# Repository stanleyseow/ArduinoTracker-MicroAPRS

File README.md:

Arduino APRS SVTrackR
=====================

 - Written by Stanley Seow ( 9W2SVT / N5SVT )
 - e-mail : stanleyseow@gmail.com
 
 *** Pls refer to the top of the source code for version history and updated instructions.

 This sketch configure the MicroAPRS (the modem) for the proper callsign and ssid and read/write data coming in from the MicroAPRS (another Arduino/atmega328P with bootloader) via Serial port

 Library needed :-
 
 * AltSoftSerial ( https://www.pjrc.com/teensy/td_libs_AltSoftSerial.html )
 * tinyGPS++ ( http://arduiniana.org/libraries/tinygpsplus/ )
 * SSD1306 OLED Text only ( https://github.com/stanleyseow/ArduinoTracker-MicroAPRS/tree/master/libraries/SSD1306_text )
 * MicroAPRS libs 
 
 Instructions :-
 
 Download the MicroAPRS compiled Modem.hex from https://github.com/markqvist/MicroAPRS/
 
 As this hex is not compiled from the Arduino IDE, you need to manually upload this hex to the Arduino with a bootloader using avrdude or Xloader.
 
Xloader to load this hex image to the Arduino / Mini Pro :-
 
    1. Download the Xloader : http://russemotto.com/xloader/
    2. Copy modem.hex into Xloader folder
    3. Select the modem hex file 
    4. Select UNO for UNO or Duemilanove/328 for Mini Pro
    5. Select the COM port and press Upload

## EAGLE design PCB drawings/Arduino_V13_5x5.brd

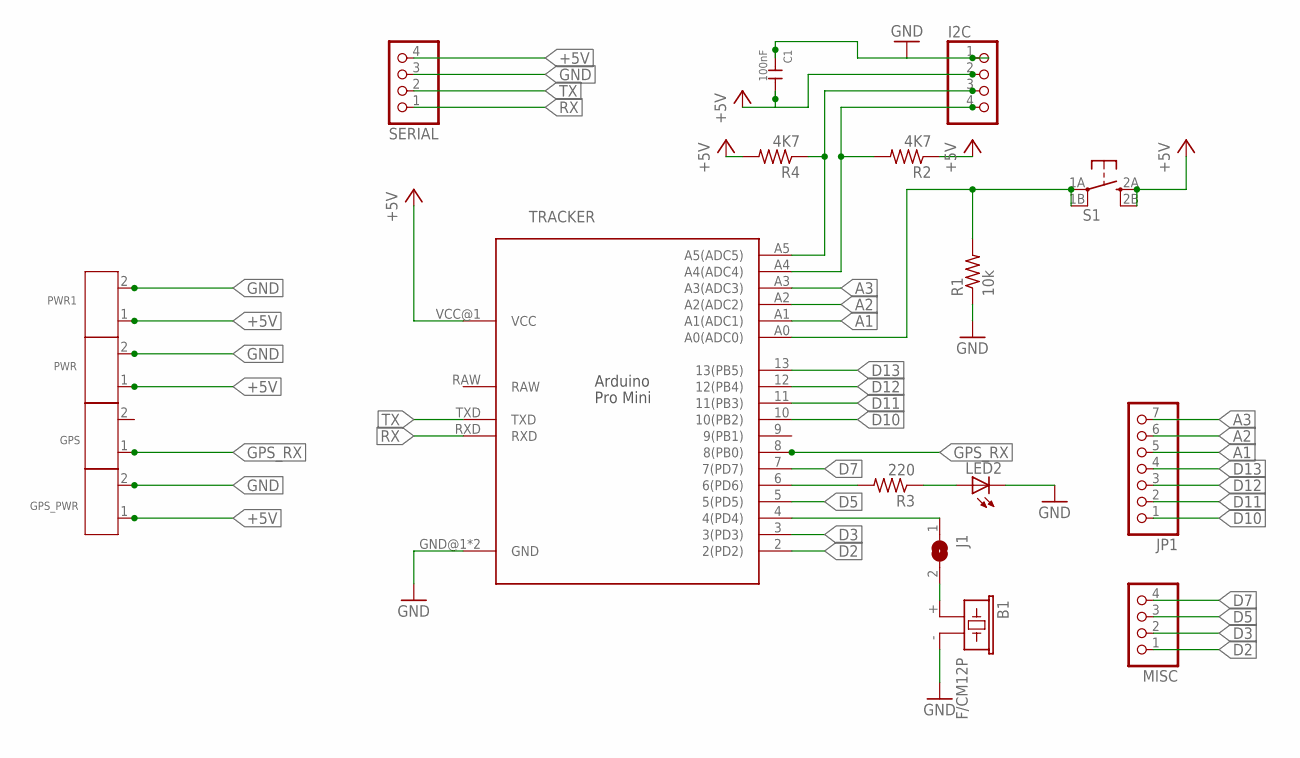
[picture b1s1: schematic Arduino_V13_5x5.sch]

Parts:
B1: F/CM12P
C1: 100nF; C1206
GPS: SCREW-TERMINAL-GREEN(2P-3.5); H2-3.5-7.0X7.0MM
GPS_PWR: SCREW-TERMINAL-GREEN(2P-3.5); H2-3.5-7.0X7.0MM
I2C: PINHD-1X4; 1X04
J1: SJ
JP1: PINHD-1X7; 1X07
LED2: LED5MM
MISC: PINHD-1X4; 1X04
PWR, PWR1: SCREW-TERMINAL-GREEN(2P-3.5); H2-3.5-7.0X7.0MM
R1: 10k; M1206
R2, R4: 4K7; M1206
R3: 220; M1206
S1: TACTILETACT-6X6-PTH; TACTILE-PTH
SERIAL: PINHD-1X4; 1X04
TRACKER: PRO-MINI

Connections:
+5V: C1.2, GPS_PWR.1, I2C.2, PWR.1, PWR1.1, R2.1, R4.2, S1.2A, S1.2B, SERIAL.4, TRACKER.VCC@1 (VCC)
A1: JP1.5, TRACKER.A1 (A1(ADC1))
A2: JP1.6, TRACKER.A2 (A2(ADC2))
A3: JP1.7, TRACKER.A3 (A3(ADC3))
A4: I2C.4, R2.2, TRACKER.A4 (A4(ADC4))
BUTTON: R1.2, S1.1A, S1.1B, TRACKER.A0 (A0(ADC0))
BUZZER: J1.1, TRACKER.4 (4(PD4))
D2: MISC.1, TRACKER.2 (2(PD2))
D3: MISC.2, TRACKER.3 (3(PD3))
D5: MISC.3, TRACKER.5 (5(PD5))
D7: MISC.4, TRACKER.7 (7(PD7))
D10: JP1.1, TRACKER.10 (10(PB2))
D11: JP1.2, TRACKER.11 (11(PB3))
D12: JP1.3, TRACKER.12 (12(PB4))
D13: JP1.4, TRACKER.13 (13(PB5))
GND: B1.- (2), C1.1, GPS_PWR.2, I2C.1, LED2.K (C), PWR.2, PWR1.2, R1.1, SERIAL.3, TRACKER.GND@1 (GND), TRACKER.GND@2 (GND)
GPS_RX: GPS.1, TRACKER.8 (8(PB0))
unnamed: I2C.3, R4.1, TRACKER.A5 (A5(ADC5))
unnamed: LED2.A, R3.1
unnamed: R3.2, TRACKER.6 (6(PD6))
unnamed: B1.+ (1), J1.2
RX: SERIAL.1, TRACKER.RXD
TX: SERIAL.2, TRACKER.TXD

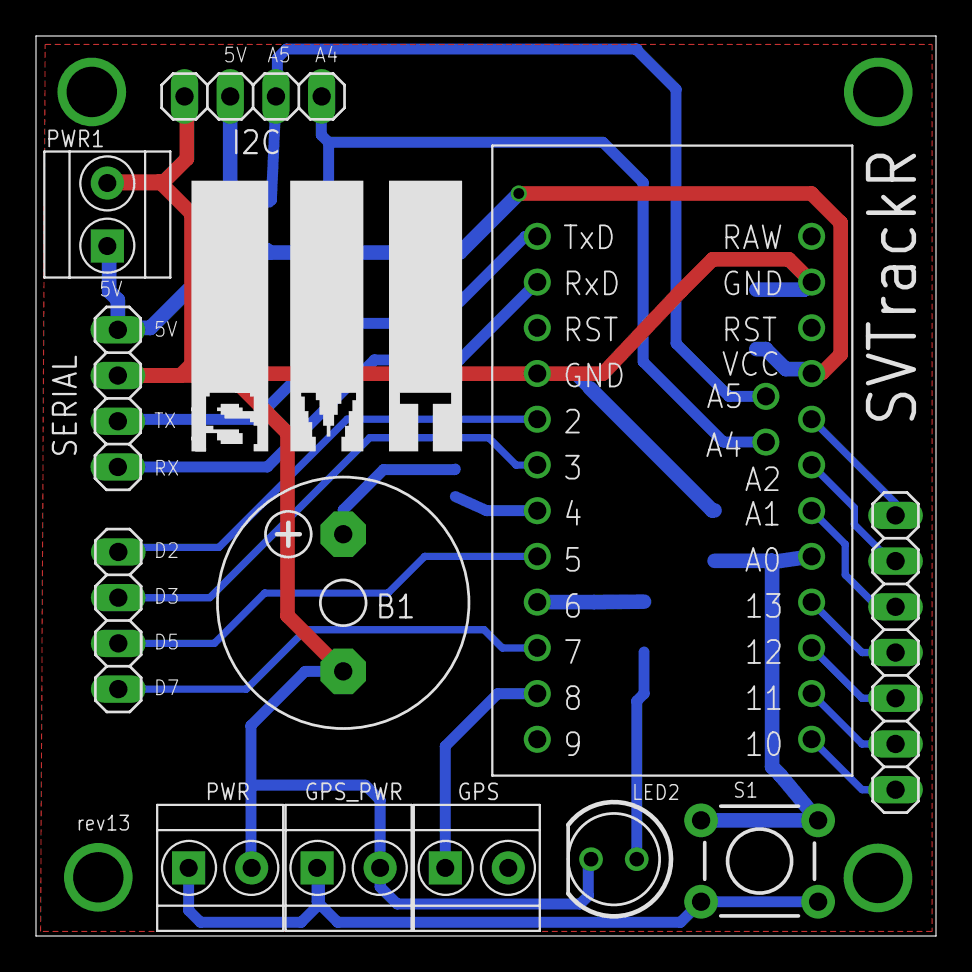
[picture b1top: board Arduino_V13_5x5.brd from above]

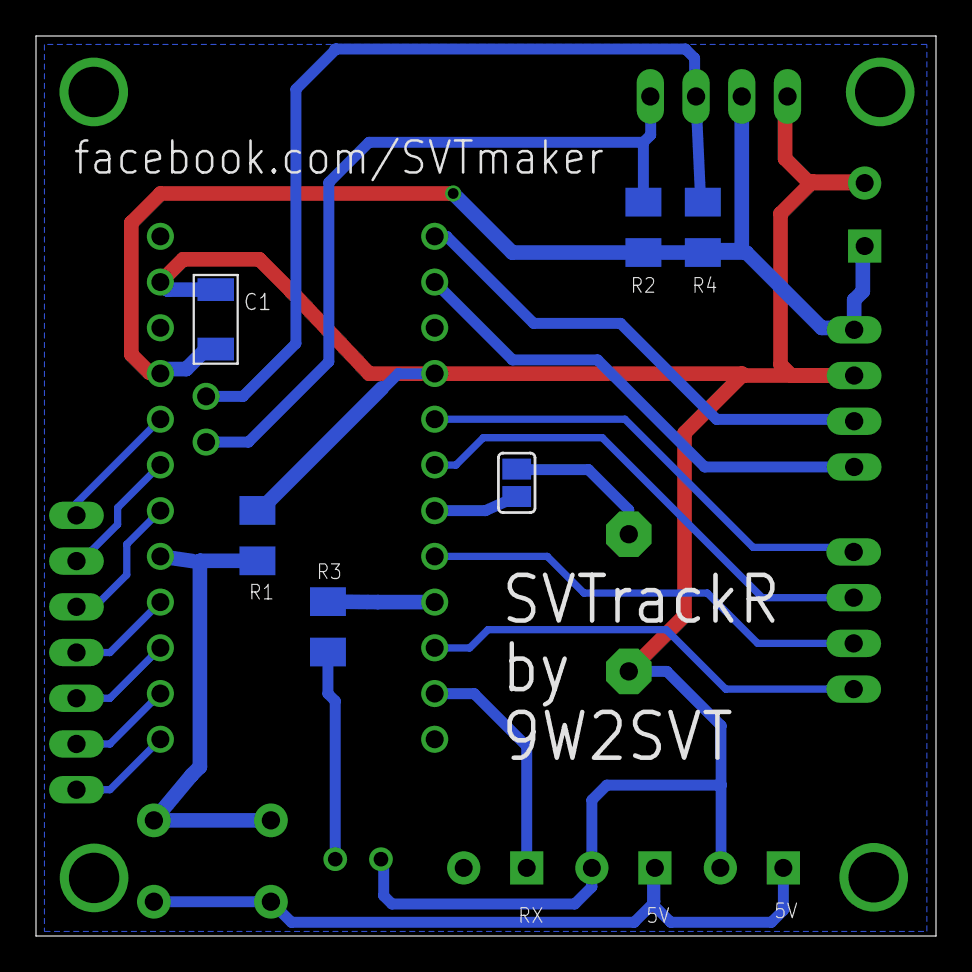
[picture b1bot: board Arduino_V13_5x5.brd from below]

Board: 2 copper layers, 50.0 x 50.0 mm, 18 parts (6 on the bottom side), 23 nets.

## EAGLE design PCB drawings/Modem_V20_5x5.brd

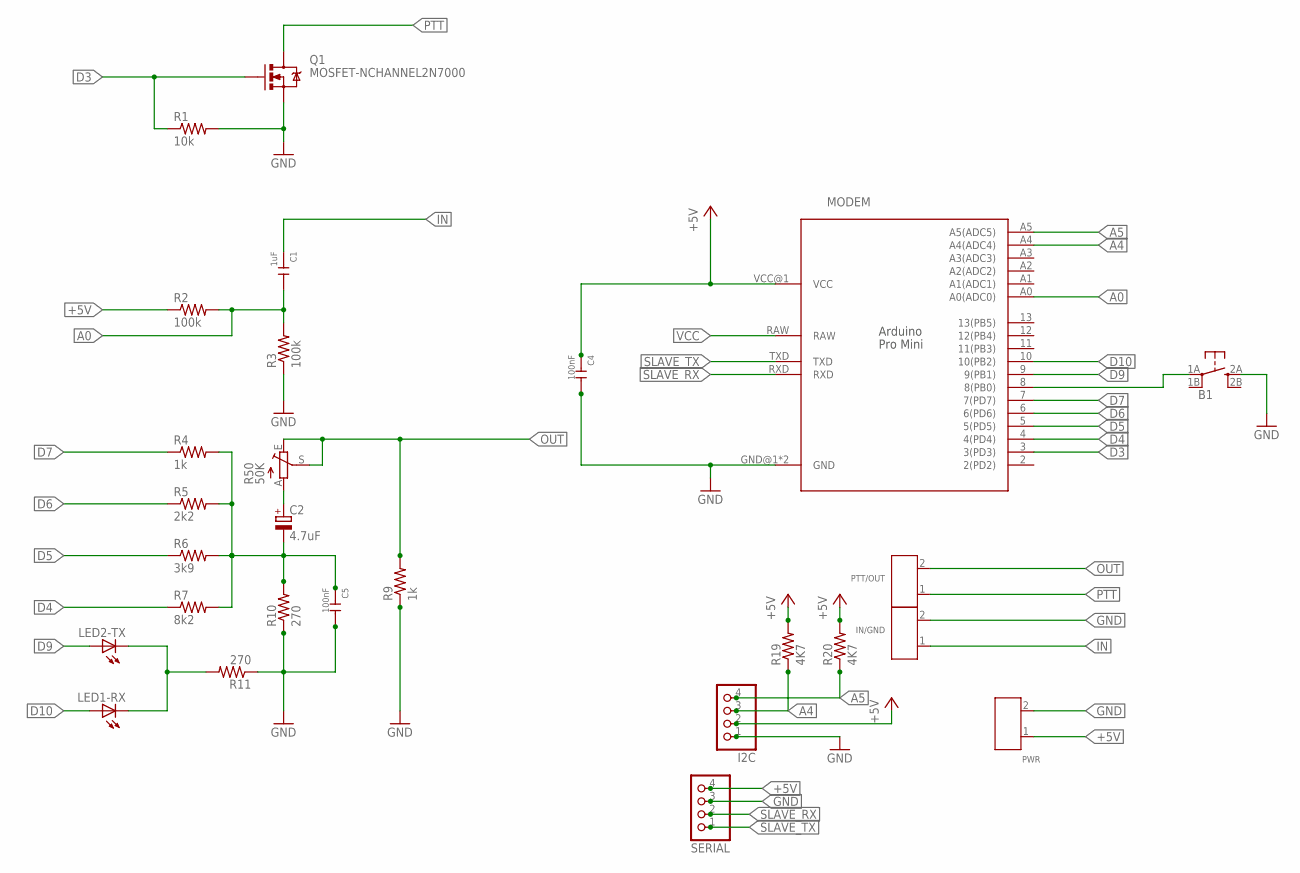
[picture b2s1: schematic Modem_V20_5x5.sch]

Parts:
B1: TACTILETACT-6X6-PTH; TACTILE-PTH
C1: 1uF; C1206
C2: 4.7uF; E2,5-6
C4, C5: 100nF; C1206
I2C: PINHD-1X4; 1X04
IN/GND: SCREW-TERMINAL-GREEN(2P-3.5); H2-3.5-7.0X7.0MM
LED1-RX, LED2-TX: LED1206; LED-1206
MODEM: PRO-MINI
PTT/OUT: SCREW-TERMINAL-GREEN(2P-3.5); H2-3.5-7.0X7.0MM
PWR: SCREW-TERMINAL-GREEN(2P-3.5); H2-3.5-7.0X7.0MM
Q1: MOSFET-NCHANNEL2N7000; TO-92
R1: 10k; R1206
R2, R3: 100k; R1206
R4, R9: 1k; R1206
R5: 2k2; R1206
R6: 3k9; R1206
R7: 8k2; R1206
R10, R11: 270; R1206
R19, R20: 4K7; R1206
R50: 50K; CA6V
SERIAL: PINHD-1X4; 1X04

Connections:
+5V: C4.1, I2C.2, MODEM.VCC@1 (VCC), PWR.1, R2.1, R19.2, R20.2, SERIAL.4
A0: C1.2, MODEM.A0 (A0(ADC0)), R2.2, R3.2
A4: I2C.3, MODEM.A4 (A4(ADC4)), R19.1
A5: I2C.4, MODEM.A5 (A5(ADC5)), R20.1
D3: MODEM.3 (3(PD3)), Q1.2 (G), R1.1
D4: MODEM.4 (4(PD4)), R7.1
D5: MODEM.5 (5(PD5)), R6.1
D6: MODEM.6 (6(PD6)), R5.1
D7: MODEM.7 (7(PD7)), R4.1
D8: B1.1A, MODEM.8 (8(PB0))
D9: LED2-TX.A, MODEM.9 (9(PB1))
D10: LED1-RX.A, MODEM.10 (10(PB2))
GND: B1.2A, C4.2, C5.2, I2C.1, IN/GND.2, MODEM.GND@1 (GND), MODEM.GND@2 (GND), PWR.2, Q1.1 (S), R1.2, R3.1, R9.1, R10.1, R11.1, SERIAL.3
IN: C1.1, IN/GND.1
unnamed: C2.+, R50.A
unnamed: LED1-RX.C, LED2-TX.C, R11.2
unnamed: C2.-, C5.1, R4.2, R5.2, R6.2, R7.2, R10.2
OUT: PTT/OUT.2, R9.2, R50.E, R50.S
PTT: PTT/OUT.1, Q1.3 (D)
SLAVE_RX: MODEM.RXD, SERIAL.2
SLAVE_TX: MODEM.TXD, SERIAL.1
VCC: MODEM.RAW

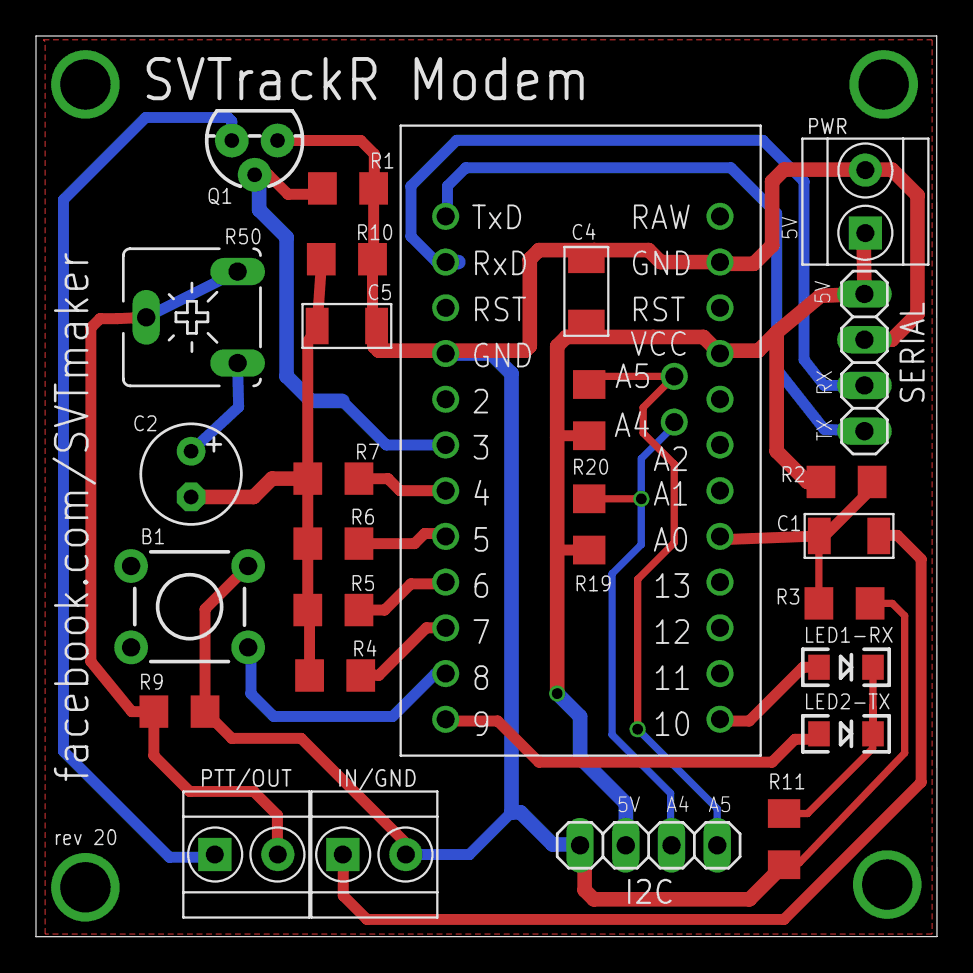
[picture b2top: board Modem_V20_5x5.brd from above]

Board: 2 copper layers, 50.1 x 50.0 mm, 27 parts (0 on the bottom side), 21 nets.

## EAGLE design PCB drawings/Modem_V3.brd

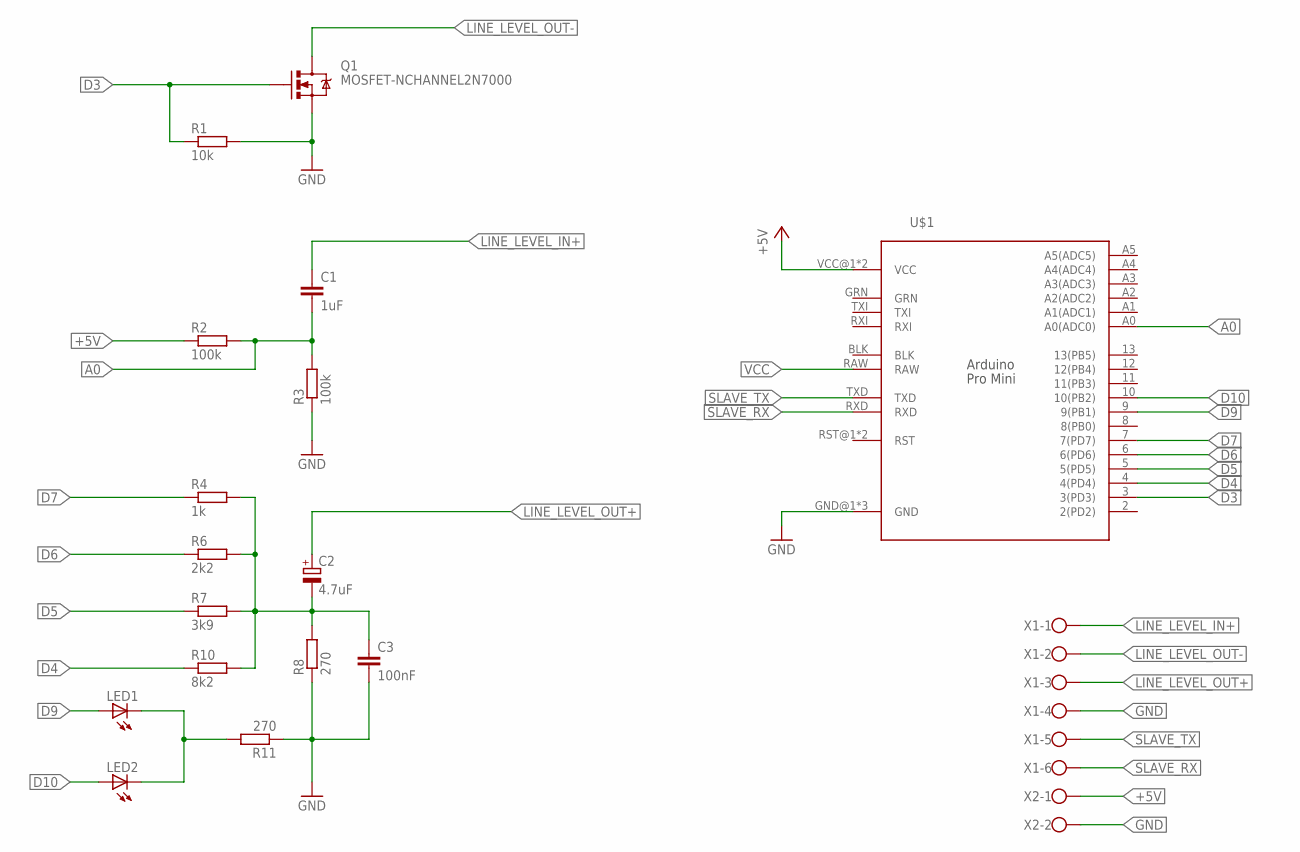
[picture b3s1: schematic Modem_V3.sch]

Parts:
C1: 1uF; C025-030X050
C2: 4.7uF; E2,5-6
C3: 100nF; C025-030X050
LED1, LED2: LED5MM
Q1: MOSFET-NCHANNEL2N7000; TO-92
R1: 10k; 0207/2V
R2, R3: 100k; 0207/2V
R4: 1k; 0207/2V
R6: 2k2; 0207/2V
R7: 3k9; 0207/2V
R8, R11: 270; 0207/2V
R10: 8k2; 0207/2V
U$1: PRO-MINI
X1: W237-6
X2: W237-102

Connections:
+5V: R2.1, U$1.VCC@1 (VCC), U$1.VCC@2 (VCC), X2.1
A0: C1.2, R2.2, R3.2, U$1.A0 (A0(ADC0))
D3: Q1.2 (G), R1.1, U$1.3 (3(PD3))
D4: R10.1, U$1.4 (4(PD4))
D5: R7.1, U$1.5 (5(PD5))
D6: R6.1, U$1.6 (6(PD6))
D7: R4.1, U$1.7 (7(PD7))
D9: LED1.A, U$1.9 (9(PB1))
D10: LED2.A, U$1.10 (10(PB2))
GND: C3.2, Q1.1 (S), R1.2, R3.1, R8.1, R11.1, U$1.GND@1 (GND), U$1.GND@2 (GND), U$1.GND@3 (GND), X1.4, X2.2
LINE_LEVEL_IN+: C1.1, X1.1
LINE_LEVEL_OUT+: C2.+, X1.3
LINE_LEVEL_OUT-: Q1.3 (D), X1.2
unnamed: LED1.K (C), LED2.K (C), R11.2
unnamed: C2.-, C3.1, R4.2, R6.2, R7.2, R8.2, R10.2
SLAVE_RX: U$1.RXD, X1.6
SLAVE_TX: U$1.TXD, X1.5
VCC: U$1.RAW

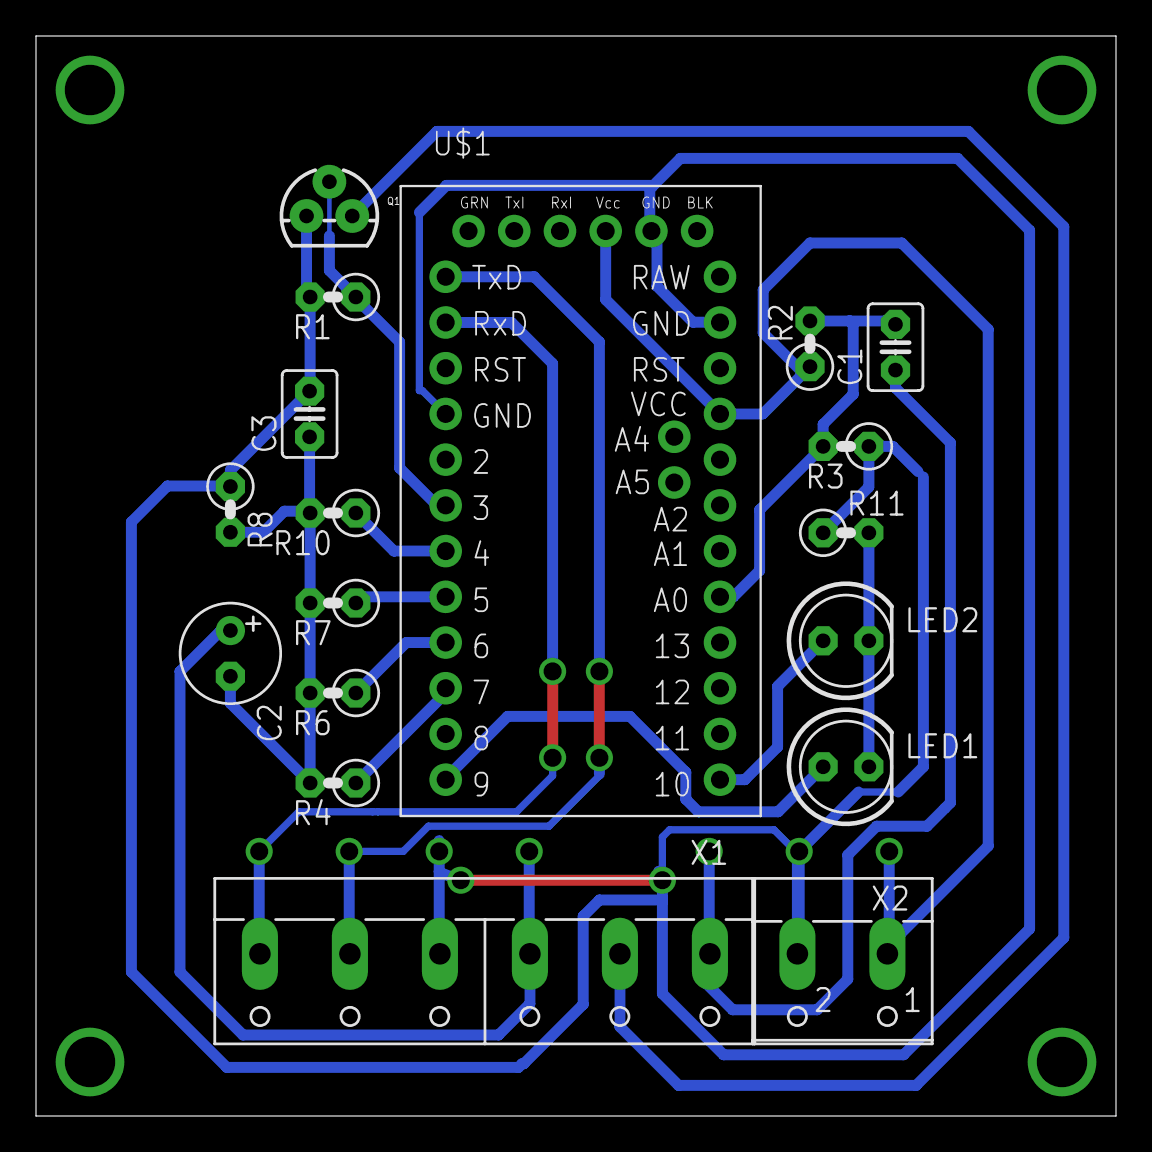
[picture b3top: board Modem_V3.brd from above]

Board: 2 copper layers, 60.0 x 60.0 mm, 18 parts (0 on the bottom side), 17 nets.

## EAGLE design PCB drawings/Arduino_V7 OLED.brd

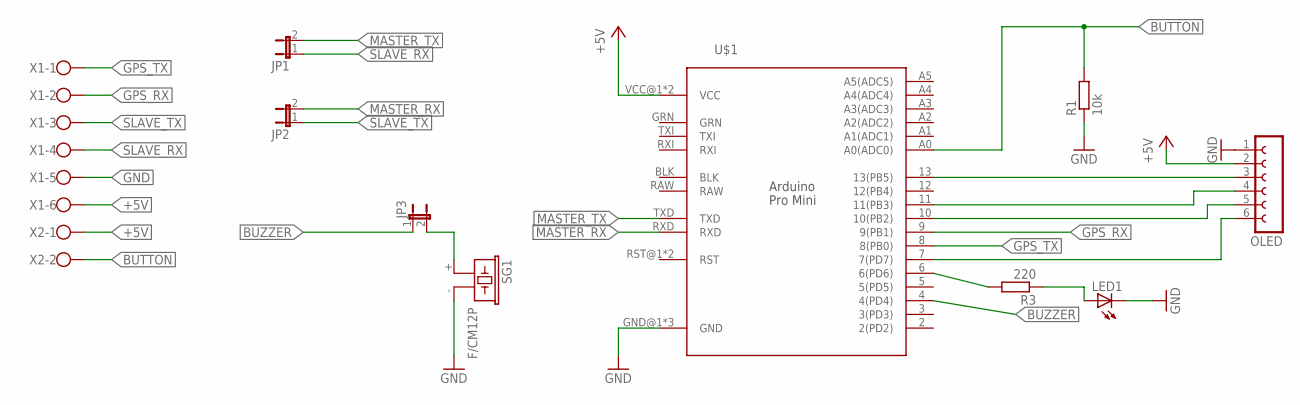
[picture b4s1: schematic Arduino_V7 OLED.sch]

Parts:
JP1, JP2, JP3: JP1E; JP1
LED1: LED5MM
OLED: FE06-1; FE06
R1: 10k; 0207/10
R3: 220; 0207/10
SG1: F/CM12P
U$1: PRO-MINI
X1: W237-6
X2: W237-102

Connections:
+5V: OLED.2, U$1.VCC@1 (VCC), U$1.VCC@2 (VCC), X1.6, X2.1
BUTTON: R1.2, U$1.A0 (A0(ADC0)), X2.2
BUZZER: JP3.1, U$1.4 (4(PD4))
CS: OLED.6, U$1.7 (7(PD7))
DI: OLED.4, U$1.11 (11(PB3))
GND: LED1.K (C), OLED.1, R1.1, SG1.- (2), U$1.GND@1 (GND), U$1.GND@2 (GND), U$1.GND@3 (GND), X1.5
GPS_RX: U$1.9 (9(PB1)), X1.2
GPS_TX: U$1.8 (8(PB0)), X1.1
MASTER_RX: JP2.2, U$1.RXD
MASTER_TX: JP1.2, U$1.TXD
unnamed: OLED.3, U$1.13 (13(PB5))
unnamed: LED1.A, R3.1
unnamed: R3.2, U$1.6 (6(PD6))
unnamed: JP3.2, SG1.+ (1)
RST: OLED.5, U$1.10 (10(PB2))
SLAVE_RX: JP1.1, X1.4
SLAVE_TX: JP2.1, X1.3

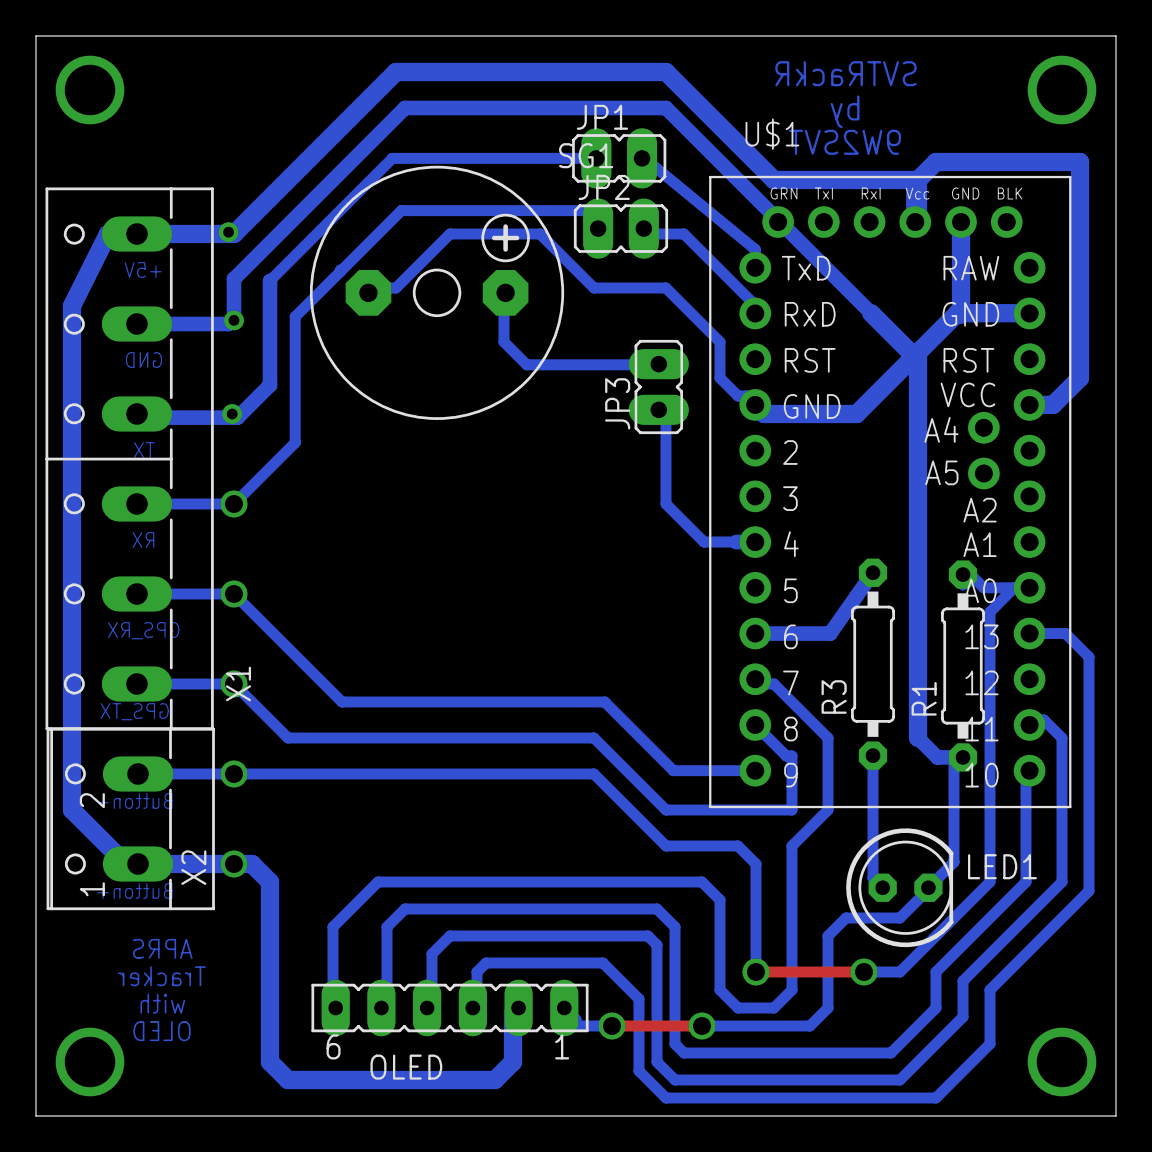
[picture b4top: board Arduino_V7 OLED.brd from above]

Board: 2 copper layers, 60.0 x 60.0 mm, 11 parts (0 on the bottom side), 17 nets.

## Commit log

2014-07-04 Initial commit
    This is the initial commit …
2014-07-04 Updated documentation...
2014-07-07 Updates and bug fixes
    Added check for gps lock, current speed and tx interval
2014-07-14 Updated to initial V0.3
    Added detection for headings and speed
2014-07-15 Updates and bug fixes 0.3a
    Fixes to course change formula
    Fixes to speed detection / Tx interval formula
    Added timestamp to debugging messages
2014-07-15 README updated
2014-07-17 Updates and bug fixes to txInternal timeout
2014-07-19 Updates to decodeAPRS() and LCD display
2014-07-22 Uploaded README
2014-08-03 Added #ifdef for LCD20x4, DEBUG and TFT22
    Added #defines, ported to Arduino Mini Pro 3.3V
2014-08-05 Added #ifdef and F() macro to reduce mem usage
    Added #define for LCD20x4, DEBUG & TFT22
2014-08-06 Added course/speed/altitude in APRS format
2014-08-08 Fixed -ve txInternal bug...
2014-08-18 Added config.h for user configurations
    Added callsign, ssid, symbol and home lat/lon to config.h file
2014-08-18 Updates README.md on Arduino library needed
2014-08-26 Updates and bug fixes
    Added sequence number to the Tx counter to check for dropped packets
2014-09-11 Upload photos
2014-09-11 Updates README
2014-09-19 Modify button codes
    Modify button action to send Status. If gps is locked, the position
    will also be sent.
2014-09-19 Updates on images ...
2014-10-14 Update to version 0.8
    - Added support for BeiDou GPS
    - Tx without GPS lock when button is pressed
2014-10-26 Updated to v 0.82
2014-11-06 Minor Updates
2014-11-20 Updated to Ver 0.9 with 0.96" OLED support
    Added 0.96” SPI OLED support
    Packet Decoding codes
    Remove all 2.2” TFT codes
2014-11-26 Added OLED/SSD1306 text only library
2014-11-26 Added OLED pics to README
2014-11-26 Updates on README
2014-11-26 Updates on photos
2014-11-26 Updates on new SVTrackR photos
2014-11-26 Updates on photos and README
2014-12-11 Updated to Ver 1.0
    Ability to decode normal / compressed packets
    Ability to display received messages to the screen
2015-01-12 Updated version to V1.1
    Added comment parsing codes from latest MicroAPRS libs
    and status ">" type parsing
2015-03-16 Added custom comments to APRS packets and fixed the hardcoding of North and East on GPS positions
2015-03-16 Fixes hardcoded padded 0 if front of Lat/Lng
    Fixes padded 0 when lat/lng less than 10
    Fixes oled display E/W and N/S
    Fixes oled display 0 padding
2015-03-26 Fixed append of zero to negative coordinates. Created beep function to save memory.
2015-04-07 Fixes hard coded 0 in Lng ... added a checking if Lng is less than 100 deg
2015-04-25 Added received stations and distance in comment field
    - add TxtoRadio with return values and tx trigger reasons ( H -
    heading, T - time, D - Distance, B - button, R - Rx station )
    - removed unused variables
    - fixes some tx timer codes
2015-04-25 Updates SSD1306_text libs to support Arduino 1.6.x
2015-04-27 Updates some photos
2015-05-03 Added Eagle CAD PCB drawings to the repo
2015-05-23 Changes OLED to large font, single line decode
2015-10-02 Upgrade to 1.62 with support for I2C 16x2LCD
    - Adding support for I2C 16x2 for Dashboard LCD
    - Added 3 screens for speed/sats/headings, date/pos and other stats
    - Added N/E/S/W into main screen
2016-05-05 Updates to V1.63
2016-10-31 Updates EagleCAD files
2017-05-15 Updated photo
2017-05-15 Upload latest photo.

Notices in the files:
parts and their libraries:
SparkFun-DiscreteSemi: Licensing: CC v3.0 Share-Alike You are welcome to use this library for commercial purposes.
